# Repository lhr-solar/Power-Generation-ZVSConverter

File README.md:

# Power-Generation-ZVSConverter
Power converter hardware design for next-gen MPPT. 
Largely based on a design made by Alex Hanson, outlined in this article:
https://ieeexplore.ieee.org/document/7749103/footnotes#footnotes-id-fn9

Ishaan added the description which has nothing to do with the project and I can't change it. :3

TODO:  
  Select opamps  
  Select gate driver/isolated converter  
  Check if nucleo DAC is sufficient. If not then add external DAC.  

Note: The "Reader" script will play a sound on completion. Don't be alarmed by it.

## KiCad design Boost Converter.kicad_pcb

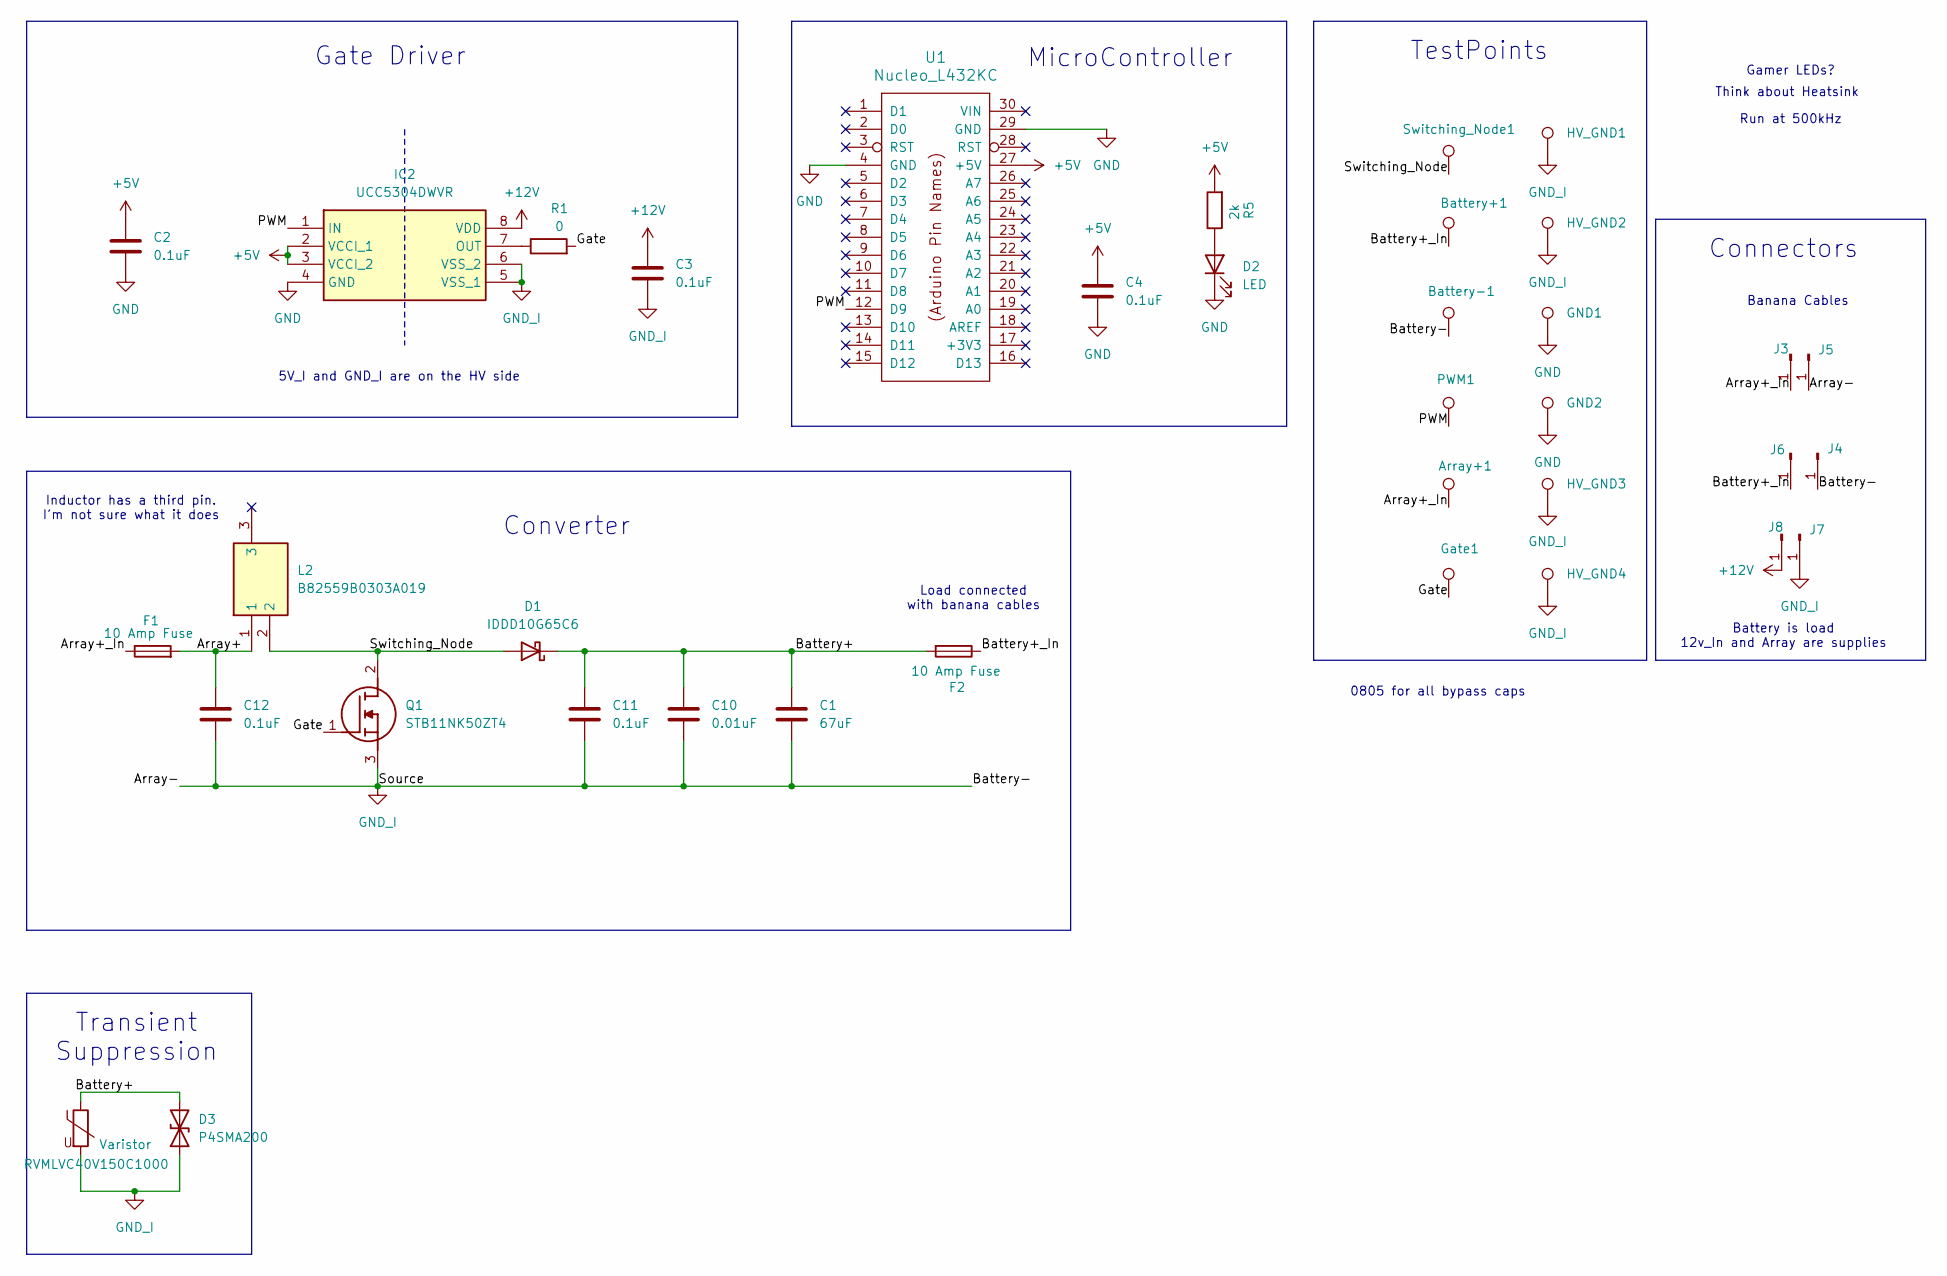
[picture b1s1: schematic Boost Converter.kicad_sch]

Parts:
Array+1: Array+; TestPoint_Bridge_Pitch2.0mm_Drill0.7mm
Battery+1: Battery+; TestPoint_Bridge_Pitch2.0mm_Drill0.7mm
Battery-1: Battery-; TestPoint_Bridge_Pitch2.0mm_Drill0.7mm
C1: 67uF; C_Disc_D6.0mm_W2.5mm_P5.00mm
C2, C3, C4, C11, C12: 0.1uF; C_0805_2012Metric
C10: 0.01uF; C_0805_2012Metric
D1: IDDD10G65C6; Infineon_PG-HDSOP-10-1
D2: LED; LED_0805_2012Metric
D3: P4SMA200; D_SMA
F1, F2: 10 Amp Fuse; LittelFuse_OMNIBLOK_520Series_PCB
GND1, GND2: Array+; TestPoint_Bridge_Pitch2.0mm_Drill0.7mm
Gate1: Array+; TestPoint_Bridge_Pitch2.0mm_Drill0.7mm
HV_GND1, HV_GND2: Array+; TestPoint_Bridge_Pitch2.0mm_Drill0.7mm
HV_GND3, HV_GND4: Array-; TestPoint_Bridge_Pitch2.0mm_Drill0.7mm
IC2: UCC5304DWVR; SOIC127P1150X280-8N; Mouser Part Number 595-UCC5304DWVR
J3, J4, J5, J6, J7, J8: Conn_01x01_Pin; 973582101
L2: B82559B0303A019; Mouser Part Number 871-B82559B0303A019
PWM1: Array+; TestPoint_Bridge_Pitch2.0mm_Drill0.7mm
Q1: STB11NK50ZT4; Manufacturer_Part_Number STB11NK50ZT4
R1: 0; C_0805_2012Metric
R5: 2k; R_0805_2012Metric
RVMLVC40V150C1000: Varistor; C_0805_2012Metric
Switching_Node1: Switching_Node; TestPoint_Bridge_Pitch2.0mm_Drill0.7mm
U1: Nucleo_L432KC; NucleoL432KC

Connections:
+5V: C2.1, C4.1, IC2.2 (VCCI_1), IC2.3 (VCCI_2), R5.2, U1.27 (+5V)
+12V: C3.1, IC2.8 (VDD), J8.1
/Array+: C12.1, F1.2, L2.1
/Array+_In: Array+1.1, F1.1, J3.1
/Battery+: C1.1, C10.1, C11.1, D1.6 (K), D1.7 (K), D1.8 (K), D1.9 (K), D1.10 (K), D3.2 (A2), F2.2, RVMLVC40V150C1000.1
/Battery+_In: Battery+1.1, F2.1, J6.1
/Gate: Gate1.1, Q1.1 (G), R1.2
/PWM: IC2.1 (IN), PWM1.1, U1.12 (D9)
/Switching_Node: D1.3 (A), D1.4 (A), D1.5 (A), L2.2, Q1.2 (D), Switching_Node1.1; also elsewhere on the board
GND: C2.2, C4.2, D2.1 (K), GND1.1, GND2.1, IC2.4 (GND), U1.4 (GND), U1.29 (GND)
GND_I: Battery-1.1, C1.2, C3.2, C10.2, C11.2, C12.2, D3.1 (A1), HV_GND1.1, HV_GND2.1, HV_GND3.1, HV_GND4.1, IC2.5 (VSS_1), IC2.6 (VSS_2), J4.1, J5.1, J7.1, Q1.3 (S), RVMLVC40V150C1000.2
unnamed: D2.2 (A), R5.1
unnamed: IC2.7 (OUT), R1.1

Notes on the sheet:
Gamer LEDs?
Gate Driver
Run at 500kHz
5V_I and GND_I are on the HV side
Load connected with banana cables
Transient Suppression
0805 for all bypass caps
Connectors
MicroController
Converter
Inductor has a third pin. I'm not sure what it does
Banana Cables
Think about Heatsink
TestPoints
Battery is load 12v_In and Array are supplies

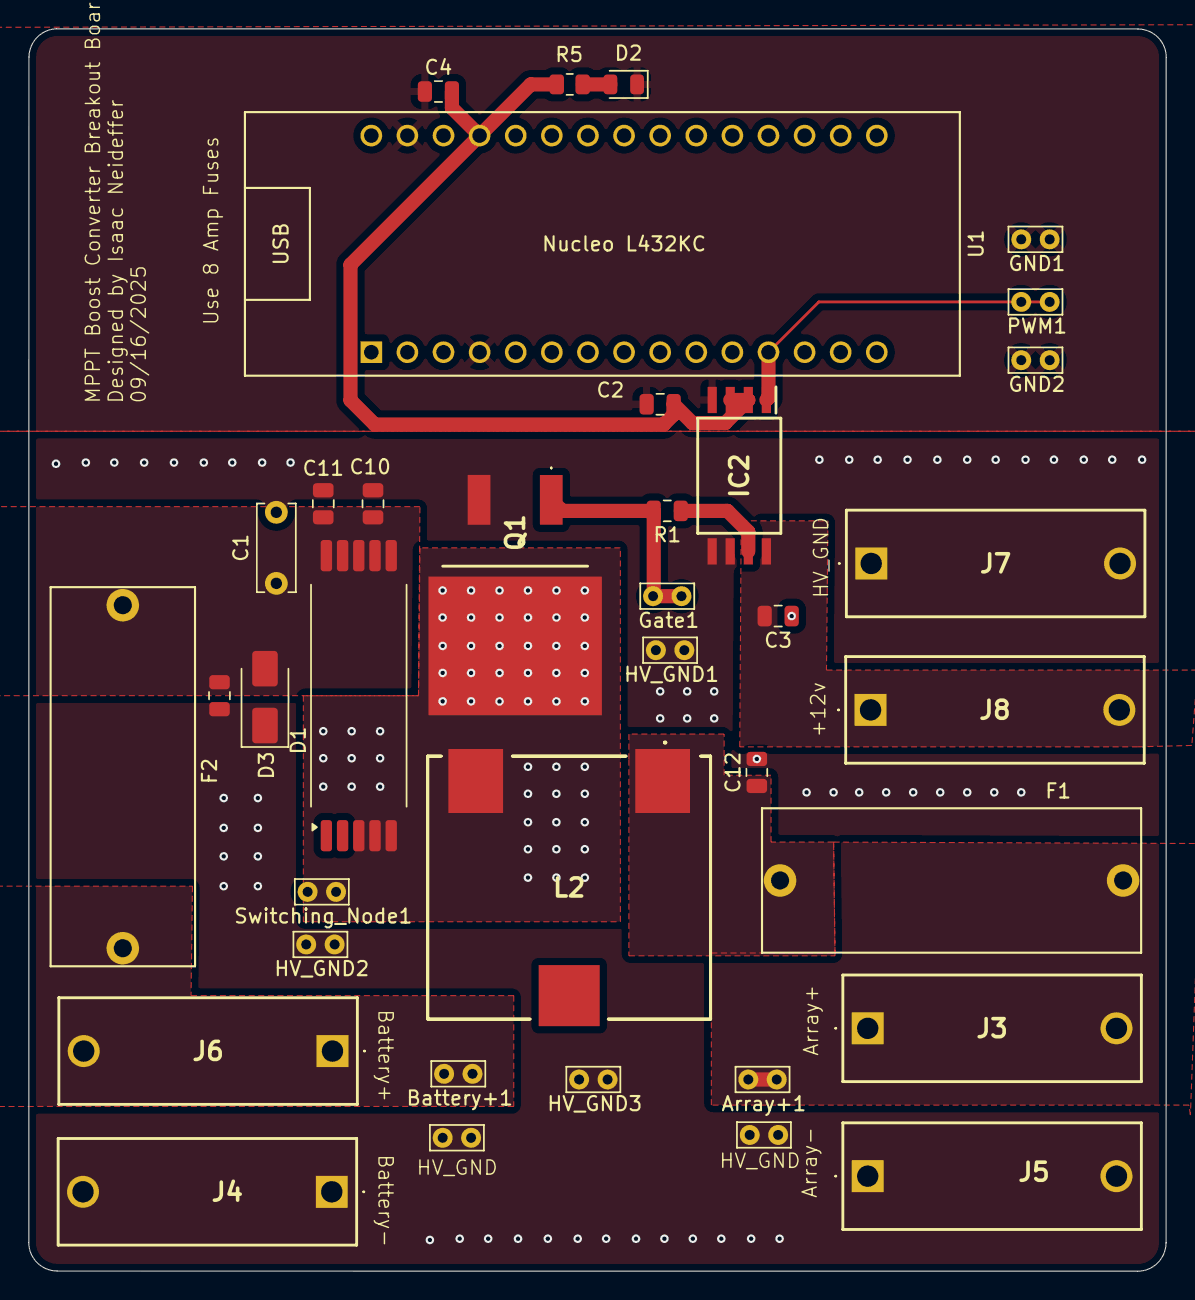
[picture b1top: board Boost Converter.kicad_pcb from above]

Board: 2 copper layers, 80.0 x 87.4 mm, 38 parts (1 on the bottom side), 13 nets.

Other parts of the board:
HS1: Heatsink_Pad; HSE01-193175P

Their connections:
/Switching_Node: HS1.1; also elsewhere on the board

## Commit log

2025-01-16 initial commit of converter schematic, only like halfway done
2025-02-19 Added Spice model for ZVS Converter as well as scripts that control batch sims and read data
2025-09-13 Changed Gan to MosFET. Added safety features. More test points. Changed gate driver to external power supply.
2025-09-16 Added varistor and tvs diode. Some other small changes.
2025-09-16 Rerouted traces to avoid inductor. Added stitching vias, and silkscreen labels
2025-09-20 New TVS diode, changed most traces to planes, added heatsink and thermal vias on mosfet. Made small adjustments to improve critical loop. Reworked some areas to shrink the board a little.
